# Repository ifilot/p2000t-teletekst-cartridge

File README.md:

# P2000T Teletekst Cartridge

## Introduction

The P2000T Teletekst Cartridge brings internet-connected teletext to the Philips
P2000T. A slot-1 ROM provides the native SAA5050 user interface, while a
Raspberry Pi Pico W or Pico 2 W interface in slot 2 manages Wi-Fi and fetches
pages from the NOS service, the P2000T community service,
[TeletekstArchief.nl](https://teletekstarchief.nl), or a user-supplied HTTP(S)
server. Together, they provide wireless network setup, optional
encrypted credential storage, and direct three-digit page selection on the
original computer.

This repository contains the public hardware and client side of the P2000T
Teletekst project:

- `src/` is the 16 KiB slot-1 cartridge client.
- `firmware/` is the Raspberry Pi Pico W firmware for the slot-2 interface.
- [`docs/protocol.md`](docs/protocol.md) defines the P2WP/2–8 link protocol
  between them.
- [`docs/custom-server.md`](docs/custom-server.md) gives the small HTTP/JSON
  contract needed to host your own pages.
- [`server/`](server/) contains a dependency-free Python example server and
  editable test page.
- `pcb/` contains the KiCad hardware design and manufacturing files.
- `enclosure/` contains the enclosure and label models.

## Downloads

Download the latest release artifacts:

- [P2000T cartridge ROM (`p2wp-cartridge.bin`)](https://github.com/ifilot/p2000t-teletekst-cartridge/releases/latest/download/p2wp-cartridge.bin)
- [Raspberry Pi Pico W firmware (`p2wp-pico-w.uf2`)](https://github.com/ifilot/p2000t-teletekst-cartridge/releases/latest/download/p2wp-pico-w.uf2)
- [Raspberry Pi Pico 2 W firmware (`p2wp-pico-2-w.uf2`)](https://github.com/ifilot/p2000t-teletekst-cartridge/releases/latest/download/p2wp-pico-2-w.uf2)

## Installing the firmware

Download all required binaries from the [Downloads](#downloads) section. Turn
the P2000T off before inserting or removing either cartridge.

### Slot-1 cartridge ROM

`p2wp-cartridge.bin` is a raw, signed 16 KiB ROM image for the slot-1
Teletekst cartridge. The programming procedure depends on the ROM, EEPROM, or
flash cartridge being used:

1. Select the exact memory device fitted to the cartridge in its programmer or
   flashing software.
2. Load `p2wp-cartridge.bin` as a raw binary. Do not byte-swap or add a file
   header.
3. Erase the device first if its technology requires it, then program and
   verify all 16,384 bytes.
4. Disconnect the programmer and insert the cartridge into slot 1 while the
   P2000T is powered off.

If the cartridge has an integrated loader rather than a removable memory chip,
follow that cartridge's instructions and use `p2wp-cartridge.bin` as its ROM
image. Do not guess a memory-device setting: an incorrect programming voltage
or pin configuration can damage the device.

### Pico W or Pico 2 W

> [!IMPORTANT]
> The Pico W and Pico 2 W use different firmware images, and the module marking
> may be hidden inside the cartridge. When the BOOTSEL drive opens in File
> Explorer, identify the Pico by its drive name: `RPI-RP2` means Pico W and
> `RP2350` means Pico 2 W. Do not copy a firmware file until the drive name has
> been checked.

| Installed module | BOOTSEL drive | Firmware file |
| --- | --- | --- |
| Raspberry Pi **Pico W** (RP2040) | `RPI-RP2` | `p2wp-pico-w.uf2` |
| Raspberry Pi **Pico 2 W** (RP2350) | `RP2350` | `p2wp-pico-2-w.uf2` |

1. Turn off the P2000T. Leave it off throughout the update.
2. Connect a data-capable USB cable to the Pico while holding its **BOOTSEL**
   button, then release the button when the USB drive appears.
3. In File Explorer (or the equivalent file manager), check the BOOTSEL drive
   name against the table above to determine which Pico variant is installed.
4. Copy the matching `.uf2` file to that drive. The drive automatically ejects
   and the Pico reboots when programming is complete.
5. Unplug the USB cable, install the slot-2 cartridge if it was removed, and
   then power on the P2000T.

BOOTSEL is stored in the Pico's read-only boot ROM, so this update method
remains available even if an earlier firmware image does not start. See the
official [Raspberry Pi drag-and-drop instructions](https://www.raspberrypi.com/documentation/microcontrollers/c_sdk.html#your-first-binaries)
for more detail.

#### Pico W versus Pico 2 W performance

Both modules provide the same cartridge features and should feel the same in
normal use. Page loading is dominated by the shared CYW43439 wireless subsystem,
Internet and server latency, and the same negotiated P2WP cartridge transport, so the
Pico 2 W's faster processor is not expected to provide a noticeable benefit
here.

## Hardware

### Enclosure

The printable enclosure and label models are available in [`enclosure/`](enclosure/).

### Circuit schematic

<p align="center">
  
</p>

## Documentation

The source menu offers NOS, P2000T Teletekst, TeletekstArchief.nl, international channels through PetsciiProxy, and a custom
server. Press `A` on that menu to choose which source should start after the
opening screen has been left untouched for 60 seconds; cycle to `UIT` to disable
auto-start. The opening prompt shows the remaining `AUTO-MODE` seconds beside
`DRUK OP EEN TOETS`. An automatic start also enables automatic next-page mode.

Choose **1 - NOS TELETEKST** for `https://teletekst-data.nos.nl`. For example,
page 101 is available at `https://teletekst-data.nos.nl/json/101-0`; the NOS
source already uses this service, so no custom server URL is needed.

Choose **4 - PETSCIIPROXY.NL** for the channels at
[`http://petsciiproxy.nl:8080`](http://petsciiproxy.nl:8080). Use `P`/`N` or the
arrow keys to browse four lists, `1`–`9` to select a channel, and `STOP` to
return. The 35 presets include ARD, ZDF, ORF, Ceefax, Teefax, Nordic and Swiss
services, and community channels. This requires updated Pico firmware supporting
P2WP/8. Channel selection lasts for the session; the saved custom URL and
autostart choice are preserved. Availability depends on the upstream service;
MTVA is omitted because upstream lists it as offline. Accented letters use
Viewdata fallbacks where the P2000T character set cannot display them.
The cartridge date/time overlay is disabled for these channels so their own
header clock remains visible. This default is configured in the cartridge ROM.

### Keymap

The on-screen help uses the P2000T's native `←` and `→` display glyphs for the
physical arrow keys. Those arrows and `P`/`N` select pages. The literal `<` and
`>` keys select the previous and next subpage; `S` selects one directly and `A`
pauses or resumes automatic rotation. `L` also toggles this subpage looping.
While paused, automatic page navigation also waits, keeping the displayed
page and subpage fixed until you resume.

| Context | Key | Action |
| --- | --- | --- |
| Page | `100`–`899` | Type three digits to fetch a page; Backspace edits an unfinished number |
| Page | `START` or `I` | Go to index page 100 |
| Page | `←` or `P`; `→` or `N` | Follow the server's previous/next-page link |
| Page | `<`; `>` | Fetch the numerically previous/advertised next subpage |
| Page | `S` | Select a subpage (`00` asks for the default subpage) |
| Page | `L` / `A` | Toggle automatic subpage looping (pause/resume) |
| Page | `V` | Toggle automatic next-page mode |
| Page | `?` or `R` | Reveal or conceal hidden text |
| Page | `Z` | Cycle normal, upper-half, and lower-half zoom |
| Page | `H` | Open the on-screen help page; any key returns |
| Page | `W` | Return to Wi-Fi setup |
| Page | `STOP` | Return to source selection |
| Source menu | `1`, `2`, `3`, `4`, or `0` | Choose NOS, P2000T, Archive, international channels, or a custom server |
| Source menu | `A` | Cycle the persistent 60-second auto-start source |
| Source menu | `H` | Open the on-screen help page |
| Input dialog | Backspace | Delete the last character or digit |
| Input dialog | Shift-`STOP` | Cancel Wi-Fi or custom-server input |

The main number row and numeric keypad both work for page and subpage entry.

Choose **0 - EIGEN SERVER** to enter an `http://` or `https://` URL of up to 96
characters, including an optional port and base path. The address is retained
in Pico flash and is filled in the next time this dialog opens. Flash is only
updated when the address changes. See [Hosting a custom Teletekst
server](docs/custom-server.md) for the required routes and response fields.

> [!WARNING]
> Certificate and hostname verification is disabled for a custom HTTPS server,
> so self-signed and private-CA certificates work. Use only a server and network
> you trust. The built-in services continue to use verified HTTPS. Archive
> requires P2WP/7 so it always uses the dedicated, verified transport.

[`docs/protocol.md`](docs/protocol.md) is the canonical P2WP/2–8 interface
specification. The Sphinx documentation also includes a
[P2000T BASIC](docs/basic.rst) client guide.

Pushes to `master` publish the rendered documentation to
[GitHub Pages](https://ifilot.github.io/p2000t-teletekst-cartridge/). Manual
deployment is also available from the GitHub Actions page. Before the first
deployment, select **GitHub Actions** as the publishing source under
**Settings → Pages**.

Build the HTML documentation with:

```sh
python3 -m pip install -r docs/requirements.txt
make -C docs html
```

## Compilation

### Quick start

From the repository root, `make run` builds the emulator and cartridge and
boots it in the emulator. This needs the dependencies listed in
[`emulator/README.md`](emulator/README.md). Append emulator options with
`ARGS`, for example `make run ARGS="--p2wp-version 2"`, or replace the network
mode with `EMUFLAGS`.

To build the cartridge ROM and firmware for both Pico W and Pico 2 W, run:

```sh
make dist
```

This produces `build/p2wp-cartridge.bin`, `build/p2wp-pico-w.uf2`, and
`build/p2wp-pico-2-w.uf2`. It requires Docker for the pinned Z88DK toolchain,
Python 3, CMake, Ninja, the ARM cross-compiler (`arm-none-eabi-gcc`), and a
Raspberry Pi Pico SDK with submodules checked out and `PICO_SDK_PATH` pointing
to it. The release workflow uses SDK 2.1.1. The emulator is not required.

To select a Python interpreter explicitly (for example, to bypass a pyenv
shim), use `make dist PYTHON=/usr/bin/python3`.

### Cartridge

Build the production C cartridge in the pinned Z88DK Docker toolchain and run
its emulator integration test with:

```sh
make -C src
make -C src smoke
```

This produces the sole release image, `build/p2wp-cartridge.bin`. See
[`src/README.md`](src/README.md) for its architecture and memory map.

### PICO Firmware

Run `make firmware` from the repository root to build both firmware variants
with the release filenames listed above.

Build the firmware with `cmake -S firmware -B firmware/build -G Ninja` followed
by `cmake --build firmware/build`; this requires `PICO_SDK_PATH` to point to a
Raspberry Pi Pico SDK.

#### Firmware stack layout

Core 0 runs Wi-Fi, lwIP and TLS; core 1 handles the P2000T mailbox. Keep the
network stack at **8 KiB or larger**, separately reserved in main RAM, and the
mailbox stack at **4 KiB or larger** in its scratch bank. The build adapts the
SDK linker script in [`firmware/cmake/network_stack.cmake`](firmware/cmake/network_stack.cmake),
limits heap growth below the network stack, checks the layout at link time,
and enables SDK stack guards on both cores. Review this adaptation when
upgrading the Pico SDK; configuration fails if the expected linker layout changes.

The original SDK default gave core 0 a 2 KiB stack reservation in a 4 KiB
scratch bank adjacent to the mailbox stack. ARM compiler analysis found an
ECDSA certificate-verification path using about 4,144 bytes on Pico W,
compared with about 3,688 bytes on Pico 2 W. Selecting the P2000T service
(option 2) can take this path and overwrite the mailbox stack on Pico W,
causing cartridge timeout `81` and subsequent "PICO W niet gevonden" errors.
A P2000T reset does not reset the Pico. Increasing only a timeout or the
stack-size macro without fixing the linker reservation does not address this.

When changing TLS configuration, compiler flags, or the SDK, check stack use
on **both boards**, including the nested ECDSA/internal-DRBG path. Host HTTP
recovery tests stub TLS and cannot detect this overflow. Hardware validation
should repeat NOS → STOP → option 2 → STOP → NOS, starting with a fully
power-cycled Pico, and confirm that page fetching and the local link remain
responsive. Also test selecting option 2 first after power-on.

The host-side replay tool fetches a live NOS response and passes it through the
same size limit and JSON-to-SAA5050 decoder as the Pico firmware:

```sh
firmware/tools/replay-nos-page 101
firmware/tools/replay-nos-page 200-2
```

For a saved response, build with `make -C firmware/tools` and run
`firmware/tools/teletekst-replay PAGE response.json [screen.bin]`. Failures are
reported as the Pico's `06`/`07` code plus the rejected decoder stage or row,
which makes captured API responses suitable as regression fixtures.

After Wi-Fi connects, firmware can securely query the repository's latest
GitHub release. Two rows beneath the post-login source menu show that online
version beside the installed cartridge and firmware versions. Both cartridge
and Pico artifacts use the repository's canonical `VERSION` value. The Pico
generation remains available to hosts through the `DEVICE_INFO` protocol command.

The emulator directly compiles the firmware's portable production command
processor. Its end-to-end cartridge tests therefore cover the same protocol
negotiation, validation, retry/sequence rules, device information, and command
dispatch used on the Pico. Deterministic host adapters replace only GPIO,
CYW43 Wi-Fi, network timing, and flash hardware.

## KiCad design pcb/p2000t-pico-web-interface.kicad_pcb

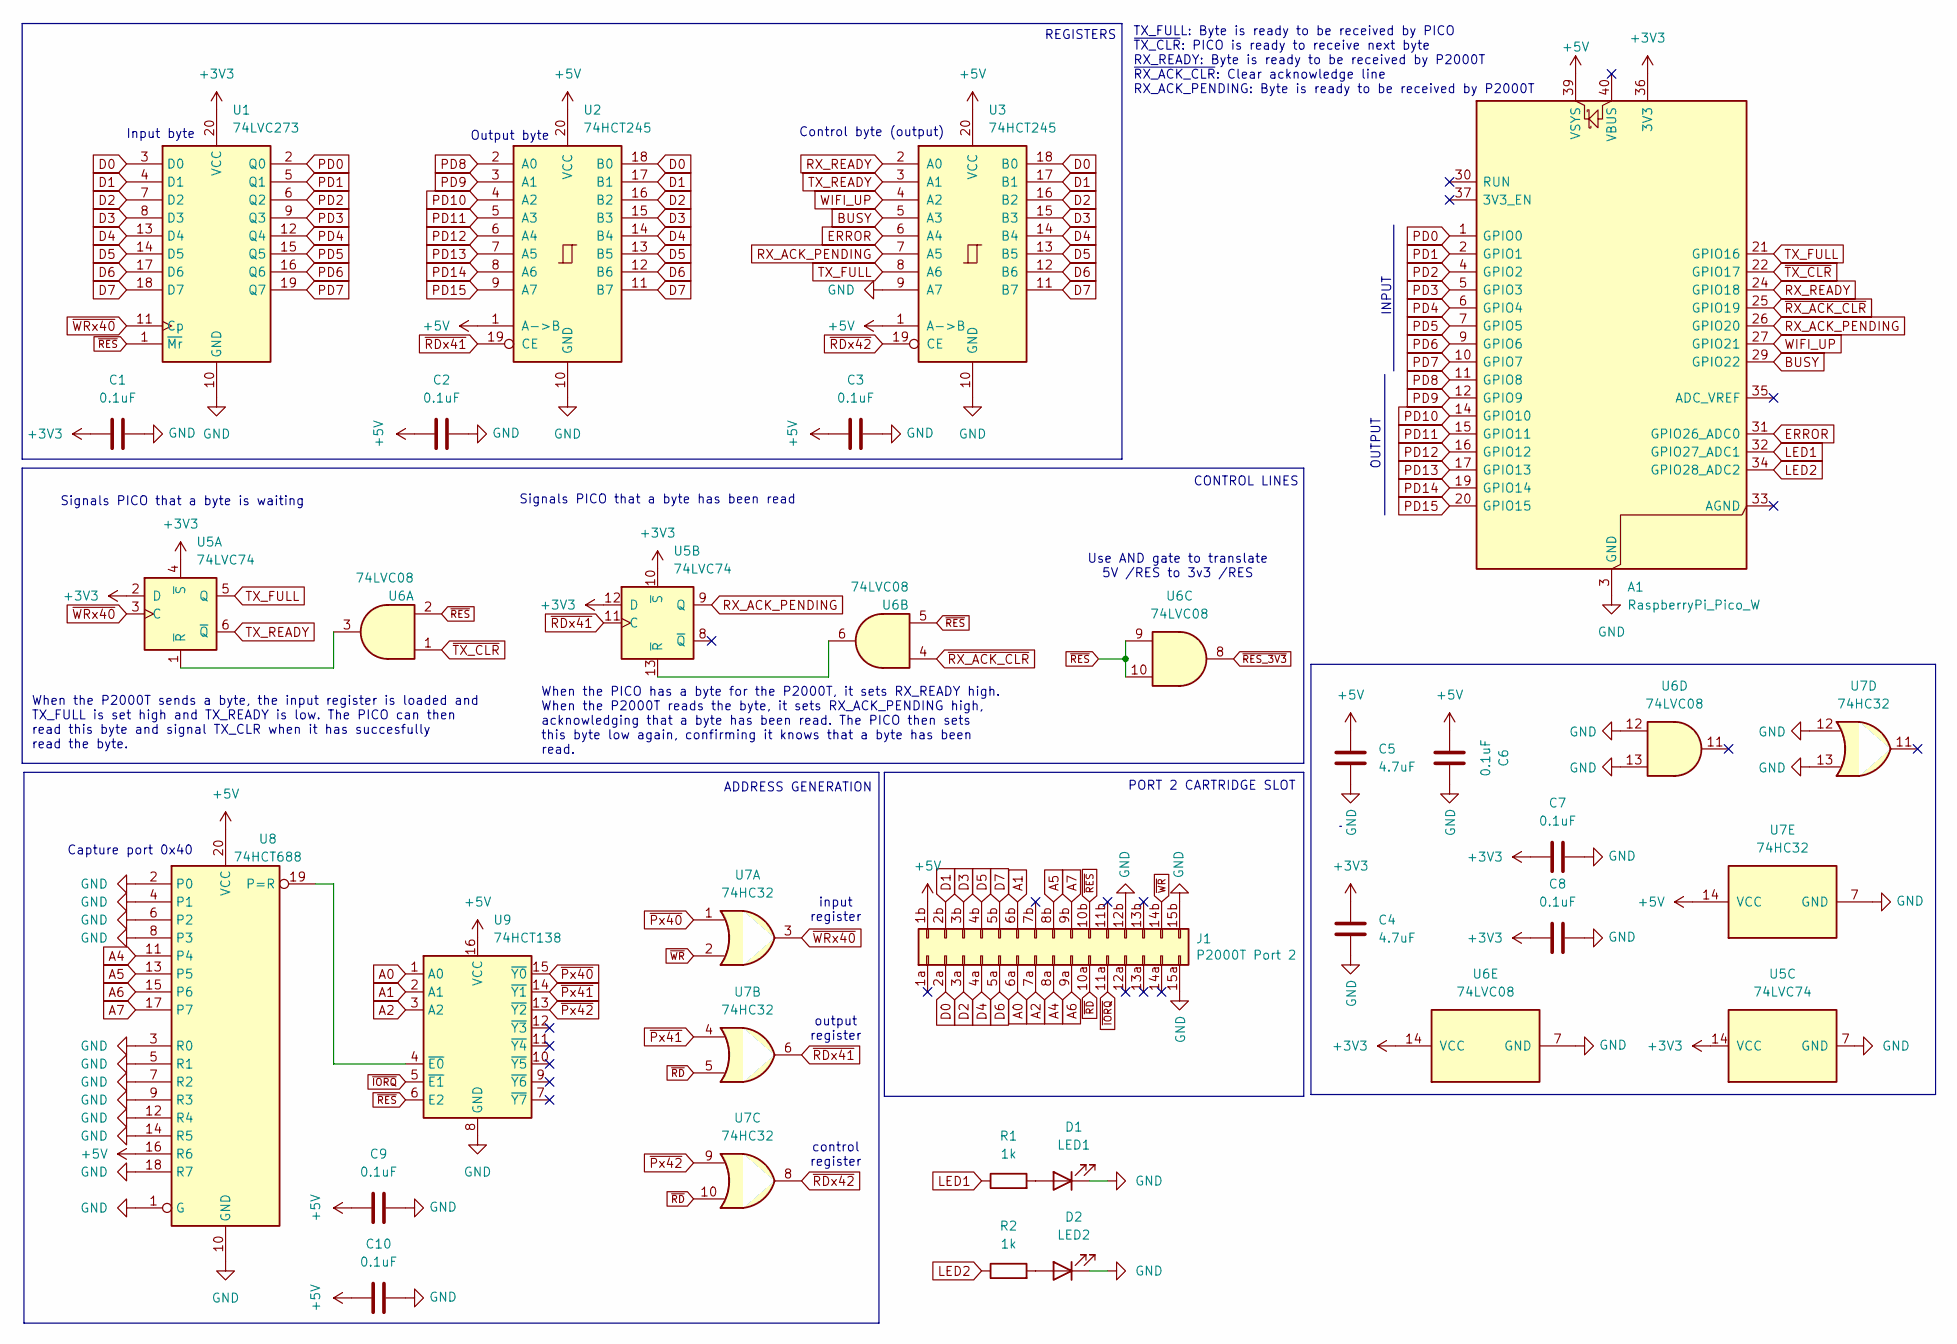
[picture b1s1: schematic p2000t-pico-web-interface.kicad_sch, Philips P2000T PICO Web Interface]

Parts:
A1: RaspberryPi_Pico_W; RaspberryPi_Pico_W_SMD_HandSolder
C1, C2, C3, C6, C7, C8, C9, C10: 0.1uF; C_0805_2012Metric
C4, C5: 4.7uF; C_1206_3216Metric
D1: LED1; LED_D5.0mm
D2: LED2; LED_D5.0mm
J1: P2000T Port 2; p2000t_cartridge_edge
R1, R2: 1k; R_Axial_DIN0207_L6.3mm_D2.5mm_P7.62mm_Horizontal
U1: 74LVC273; SOIC-20W_7.5x12.8mm_P1.27mm
U2, U3: 74HCT245; SOIC-20W_7.5x12.8mm_P1.27mm
U5: 74LVC74; SO-14_3.9x8.65mm_P1.27mm
U6: 74LVC08; SO-14_3.9x8.65mm_P1.27mm
U7: 74HC32; SO-14_3.9x8.65mm_P1.27mm
U8: 74HCT688; SOIC-20W_7.5x12.8mm_P1.27mm
U9: 74HCT138; SO-16_3.9x9.9mm_P1.27mm

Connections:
+3V3: A1.36 (3V3), C1.1, C4.1, C7.1, C8.1, U1.20 (VCC), U5.2 (D), U5.4 (~S), U5.10 (~S), U5.12 (D), U5.14 (VCC), U6.14 (VCC)
+5V: A1.39 (VSYS), C2.1, C3.1, C5.1, C6.1, C9.1, C10.1, J1.1b, U2.1 (A->B), U2.20 (VCC), U3.1 (A->B), U3.20 (VCC), U7.14 (VCC), U8.16 (R6), U8.20 (VCC), U9.16 (VCC)
A0: J1.6a, U9.1 (A0)
A1: J1.6b, U9.2 (A1)
A2: J1.7a, U9.3 (A2)
A4: J1.8a, U8.11 (P4)
A5: J1.8b, U8.13 (P5)
A6: J1.9a, U8.15 (P6)
A7: J1.9b, U8.17 (P7)
BUSY: A1.29 (GPIO22), U3.5 (A3)
D0: J1.2a, U1.3 (D0), U2.18 (B0), U3.18 (B0)
D1: J1.2b, U1.4 (D1), U2.17 (B1), U3.17 (B1)
D2: J1.3a, U1.7 (D2), U2.16 (B2), U3.16 (B2)
D3: J1.3b, U1.8 (D3), U2.15 (B3), U3.15 (B3)
D4: J1.4a, U1.13 (D4), U2.14 (B4), U3.14 (B4)
D5: J1.4b, U1.14 (D5), U2.13 (B5), U3.13 (B5)
D6: J1.5a, U1.17 (D6), U2.12 (B6), U3.12 (B6)
D7: J1.5b, U1.18 (D7), U2.11 (B7), U3.11 (B7)
ERROR: A1.31 (GPIO26_ADC0), U3.6 (A4)
GND: A1.3 (GND), A1.8 (GND), A1.13 (GND), A1.18 (GND), A1.23 (GND), A1.28 (GND), A1.38 (GND), C1.2, C2.2, C3.2, C4.2, C5.2, C6.2, C7.2, C8.2, C9.2, C10.2, D1.1 (K), D2.1 (K), J1.12b, J1.15a, J1.15b, U1.10 (GND), U2.10 (GND), U3.9 (A7), U3.10 (GND), U5.7 (GND), U6.7 (GND), U6.12, U6.13, U7.7 (GND), U7.12, U7.13, U8.1 (G), U8.2 (P0), U8.3 (R0), U8.4 (P1), U8.5 (R1), U8.6 (P2), U8.7 (R2), U8.8 (P3), U8.9 (R3), U8.10 (GND), U8.12 (R4), U8.14 (R5), U8.18 (R7), U9.8 (GND)
LED1: A1.32 (GPIO27_ADC1), R1.1
LED2: A1.34 (GPIO28_ADC2), R2.1
unnamed: D1.2 (A), R1.2
unnamed: D2.2 (A), R2.2
unnamed: U5.1 (~R), U6.3
unnamed: U5.13 (~R), U6.6
unnamed: U8.19 (P=R), U9.4 (~E0)
PD0: A1.1 (GPIO0), U1.2 (Q0)
PD1: A1.2 (GPIO1), U1.5 (Q1)
PD2: A1.4 (GPIO2), U1.6 (Q2)
PD3: A1.5 (GPIO3), U1.9 (Q3)
PD4: A1.6 (GPIO4), U1.12 (Q4)
PD5: A1.7 (GPIO5), U1.15 (Q5)
PD6: A1.9 (GPIO6), U1.16 (Q6)
PD7: A1.10 (GPIO7), U1.19 (Q7)
PD8: A1.11 (GPIO8), U2.2 (A0)
PD9: A1.12 (GPIO9), U2.3 (A1)
PD10: A1.14 (GPIO10), U2.4 (A2)
PD11: A1.15 (GPIO11), U2.5 (A3)
PD12: A1.16 (GPIO12), U2.6 (A4)
PD13: A1.17 (GPIO13), U2.7 (A5)
PD14: A1.19 (GPIO14), U2.8 (A6)
PD15: A1.20 (GPIO15), U2.9 (A7)
RX_ACK_PENDING: A1.26 (GPIO20), U3.7 (A5), U5.9 (Q)
RX_READY: A1.24 (GPIO18), U3.2 (A0)
TX_FULL: A1.21 (GPIO16), U3.8 (A6), U5.5 (Q)
TX_READY: U3.3 (A1), U5.6 (~Q)
WIFI_UP: A1.27 (GPIO21), U3.4 (A2)
~IORQ: J1.11a, U9.5 (~E1)
~Px40: U7.1, U9.15 (~Y0)
~Px41: U7.4, U9.14 (~Y1)
~Px42: U7.9, U9.13 (~Y2)
~RDx41: U2.19 (CE), U5.11 (C), U7.6
~RDx42: U3.19 (CE), U7.8
~RD: J1.10a, U7.5, U7.10
~RES_3V3: U6.8
~RES: J1.10b, U1.1 (~Mr), U6.2, U6.5, U6.9, U6.10, U9.6 (E2)
~RX_ACK_CLR: A1.25 (GPIO19), U6.4
~TX_CLR: A1.22 (GPIO17), U6.1
~WRx40: U1.11 (Cp), U5.3 (C), U7.3
~WR: J1.14b, U7.2

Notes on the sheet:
input register
Capture port 0x40
TX_FULL: Byte is ready to be received by PICO ~{TX_CLR}: PICO is ready to receive next byte RX_READY: Byte is ready to be received by P2000T ~{RX_ACK_CLR}: Clear acknowledge line RX_ACK_PENDING: Byte is ready to be received by P2000T
output register
When the P2000T sends a byte, the input register is loaded and TX_FULL is set high and TX_READY is low. The PICO can then read this byte and signal TX_CLR when it has succesfully read the byte.
OUTPUT
CONTROL LINES
When the PICO has a byte for the P2000T, it sets RX_READY high. When the P2000T reads the byte, it sets RX_ACK_PENDING high, acknowledging that a byte has been read. The PICO then sets this byte low again, confirming it knows that a byte has been read.
control register
Signals PICO that a byte has been read
Input byte
Use AND gate to translate 5V /RES to 3v3 /RES
ADDRESS GENERATION
Output byte
REGISTERS
PORT 2 CARTRIDGE SLOT
Signals PICO that a byte is waiting
INPUT
Control byte (output)

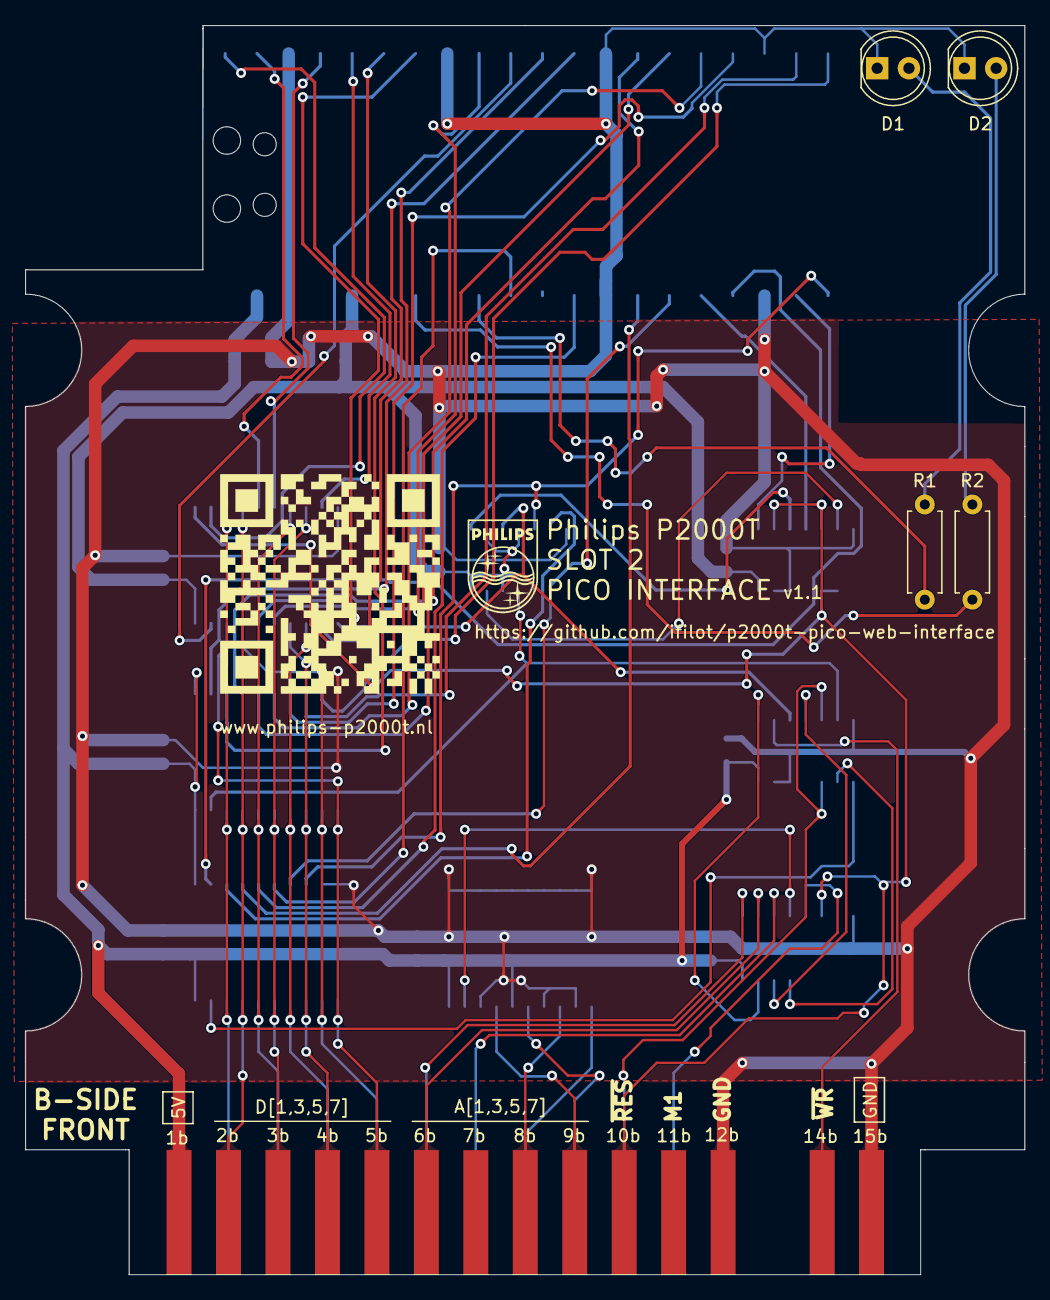
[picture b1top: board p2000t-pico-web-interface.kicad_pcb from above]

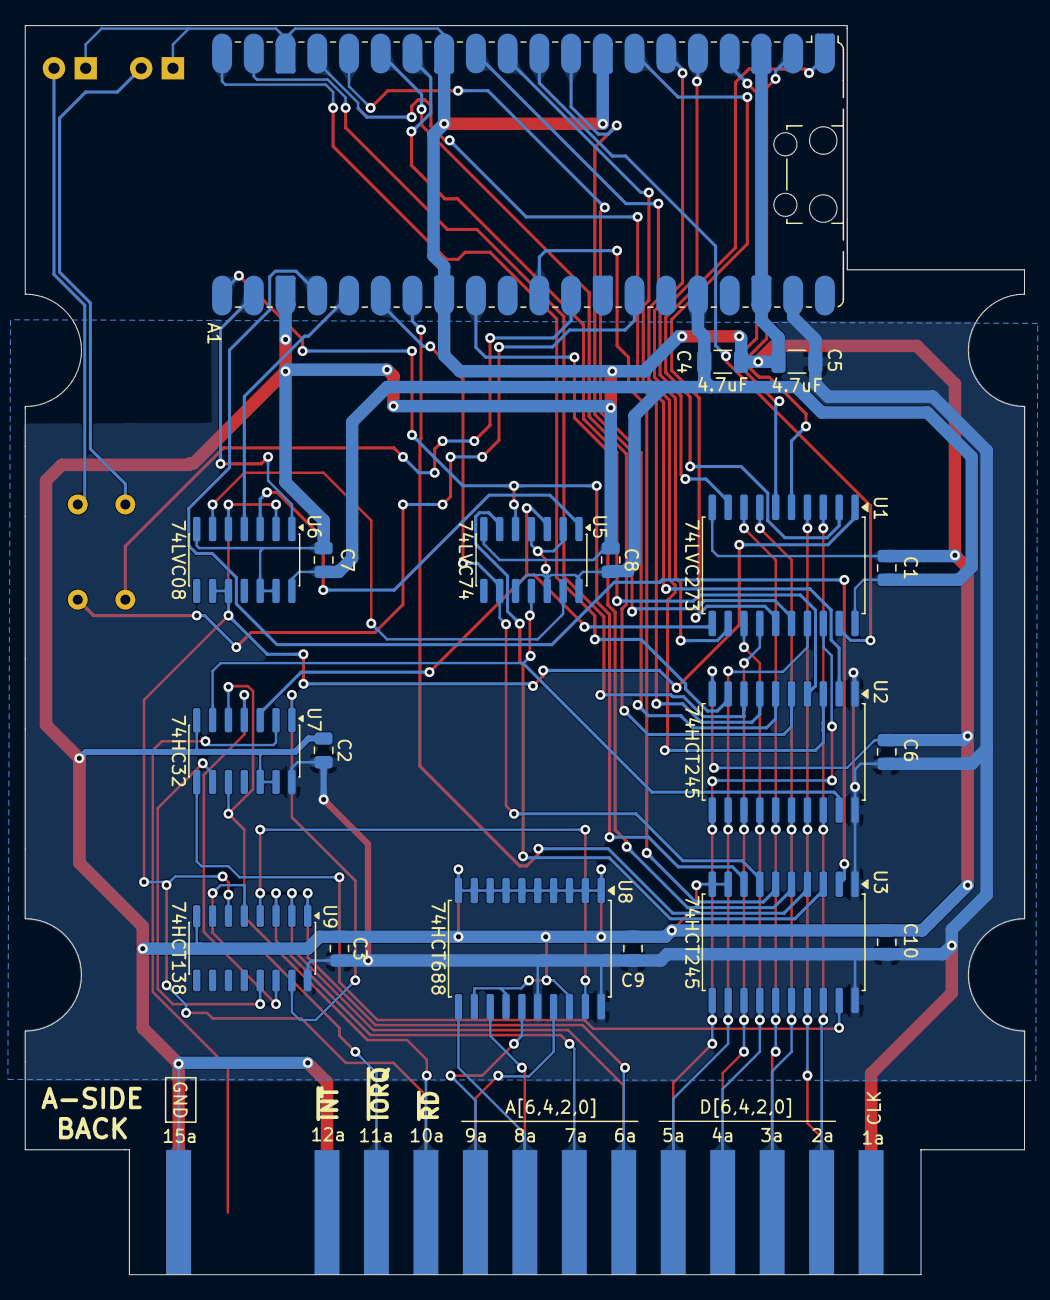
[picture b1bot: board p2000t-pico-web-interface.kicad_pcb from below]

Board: 2 copper layers, 80.0 x 100.0 mm, 26 parts (20 on the bottom side), 60 nets.

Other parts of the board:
G002: LOGO; qrcode
G003: LOGO; philips_logo

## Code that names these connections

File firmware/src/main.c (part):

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enum {
    GPIO_HOST_DATA_BASE = 0,
    GPIO_PICO_DATA_BASE = 8,
    GPIO_TX_FULL = 16,
    GPIO_TX_CLEAR_N = 17,
    GPIO_RX_READY = 18,
    GPIO_RX_ACK_CLEAR_N = 19,
    GPIO_RX_ACK_PENDING = 20,
    GPIO_WIFI_UP = 21,
    GPIO_BUSY = 22,
    GPIO_ERROR = 26,
};
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    const bool connected = wifi_connection_state == WIFI_CONNECTED;
    mutex_exit(&wifi_mutex);
    ntp_service(connected);
    gpio_put(GPIO_WIFI_UP, connected);
}

/**
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            wifi_connection_state = WIFI_CONNECTING;
            wifi_connect_requested = true;
            mutex_exit(&wifi_mutex);
            gpio_put(GPIO_WIFI_UP, false);
        }
        mbedtls_platform_zeroize(&credentials, sizeof(credentials));
    } else if (operation == WIFI_PROFILE_OPERATION_SAVE) {
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    mutex_exit(&wifi_mutex);

    if (!available) {
        gpio_put(GPIO_WIFI_UP, false);
        while (true) {
            tight_loop_contents();
        }
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    mutex_exit(&wifi_mutex);

    if (failed) {
        gpio_put(GPIO_WIFI_UP, false);
    }
}

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/**
 * @brief Configure the parallel mailbox bus and clear stale handshake state.
 *
 * Data directions follow the external latches: GPIO0-7 are host-to-Pico input,
 * while GPIO8-15 are Pico-to-host output.
 */
static void mailbox_init(void) {
    for (uint gpio = GPIO_HOST_DATA_BASE; gpio < GPIO_HOST_DATA_BASE + 8u; ++gpio) {
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        init_output(gpio, false);
    }

    gpio_init(GPIO_TX_FULL);
    gpio_set_dir(GPIO_TX_FULL, GPIO_IN);
    gpio_disable_pulls(GPIO_TX_FULL);

    gpio_init(GPIO_RX_ACK_PENDING);
    gpio_set_dir(GPIO_RX_ACK_PENDING, GPIO_IN);
    gpio_disable_pulls(GPIO_RX_ACK_PENDING);

    init_output(GPIO_TX_CLEAR_N, true);
    init_output(GPIO_RX_READY, false);
    init_output(GPIO_RX_ACK_CLEAR_N, true);
    init_output(GPIO_WIFI_UP, false);
    init_output(GPIO_BUSY, false);
    init_output(GPIO_ERROR, false);

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 * @return true when a byte was present and acknowledged.
 */
static bool mailbox_try_receive(uint8_t *byte) {
    if (!gpio_get(GPIO_TX_FULL)) {
        return false;
    }

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    *byte = (uint8_t)(gpio_get_all() & HOST_DATA_MASK);

    gpio_put(GPIO_TX_CLEAR_N, false);
    (void)wait_for_gpio(GPIO_TX_FULL, false, 1);
    gpio_put(GPIO_TX_CLEAR_N, true);
    return true;
}
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 * @return true after the host acknowledges and releases the byte.
 */
static bool mailbox_send_byte(uint8_t byte) {
    if (!wait_for_gpio(GPIO_RX_ACK_PENDING, false, BYTE_TIMEOUT_MS)) {
        return false;
    }

    gpio_put_masked(PICO_DATA_MASK, (uint32_t)byte << GPIO_PICO_DATA_BASE);
    busy_wait_us_32(1);
    gpio_put(GPIO_RX_READY, true);

    if (!wait_for_gpio(GPIO_RX_ACK_PENDING, true, BYTE_TIMEOUT_MS)) {
        gpio_put(GPIO_RX_READY, false);
        return false;
    }

    // READY must fall before the acknowledgement is cleared, otherwise the
    // host could accept the same byte for a second time.
    gpio_put(GPIO_RX_READY, false);
    gpio_put(GPIO_RX_ACK_CLEAR_N, false);
    const bool cleared = wait_for_gpio(GPIO_RX_ACK_PENDING, false, 1);
    gpio_put(GPIO_RX_ACK_CLEAR_N, true);
    return cleared;
}
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    wifi_connection_state = WIFI_CONNECTING;
    wifi_connect_requested = true;
    mutex_exit(&wifi_mutex);
    gpio_put(GPIO_WIFI_UP, false);
    response->payload_length = 0u;
    return P2WP_FIRMWARE_COMMAND_OK;
}
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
